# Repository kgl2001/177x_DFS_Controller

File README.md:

# Acorn BBC Micro 177x Disc Interface module
This module can be used in place of a 8271 disc controller in the BBC micro computer.

Some general notes:

* The source files are to be used with KiCAD v9.0.0 or later.
* The Rev03 PCB is only marginally bigger than the original 8271 IC that it replaces. This should prevent the board from clashing with other upgrades, like Speech or ROM / RAM expansion boards.
* The gerber files have been optimised for fabrication by JLCPCB. In particular, there is a 8mmx8mm silkscreen box on the top front of the PCB. This is to allow a 2D barcode, with unique serial number to be printed on the PCB.
* If you want the barcode to be added, then make sure to select this option in the 'Mark on PCB' field, and make sure to select 'Specify position' in the '2D Barcode Position' field, otherwise you will end up with a white 8mm x 8mm box printed on your PCB and a 8mm x 8mm barcode printed at a position of JLCPCBs choosing. Thrust me on this!
* If you don't want the barcode added, then remove the 8mm x 8mm box from the silkscreen layer and regenerate the gerbers. Otherwise you will end up with a white 8mm x 8mm box printed on your PCB.
* A combined CPL / BOM file is included in the gerber directory. Again, this is for use with JLCPCB, if you want to use their PCBA (PCB Assembly) to solder on all the SMD parts.
* You will need to source a suitable 1770 / 1772 disc controller IC to install on the board. These are becoming increasingly difficult to find at a reasonable price.
* Additional modifications (including the installation of additional ICs) may be required to the beeb motherboard. These modifications are detailed in the attached Acorn_1770DiscIFUpgradeKit.pdf document 

Please refer to the following discussion on Stardot for further details: [https://stardot.org.uk/forums/viewtopic.php?f=3&t=18815](https://stardot.org.uk/forums/viewtopic.php?t=30150)

## Author

The Disc Interface module is developed and maintained by Ken Lowe.
    
## Hardware License (Creative Commons BY-SA 4.0)

Please see the following link for details: https://creativecommons.org/licenses/by-sa/4.0/

You are free to:

Share - copy and redistribute the material in any medium or format
Adapt - remix, transform, and build upon the material
for any purpose, even commercially.

This license is acceptable for Free Cultural Works.

The licensor cannot revoke these freedoms as long as you follow the license terms.

Under the following terms:

Attribution - You must give appropriate credit, provide a link to the license, and indicate if changes were made. You may do so in any reasonable manner, but not in any way that suggests the licensor endorses you or your use.

ShareAlike - If you remix, transform, or build upon the material, you must distribute your contributions under the same license as the original.

No additional restrictions - You may not apply legal terms or technological measures that legally restrict others from doing anything the license permits.

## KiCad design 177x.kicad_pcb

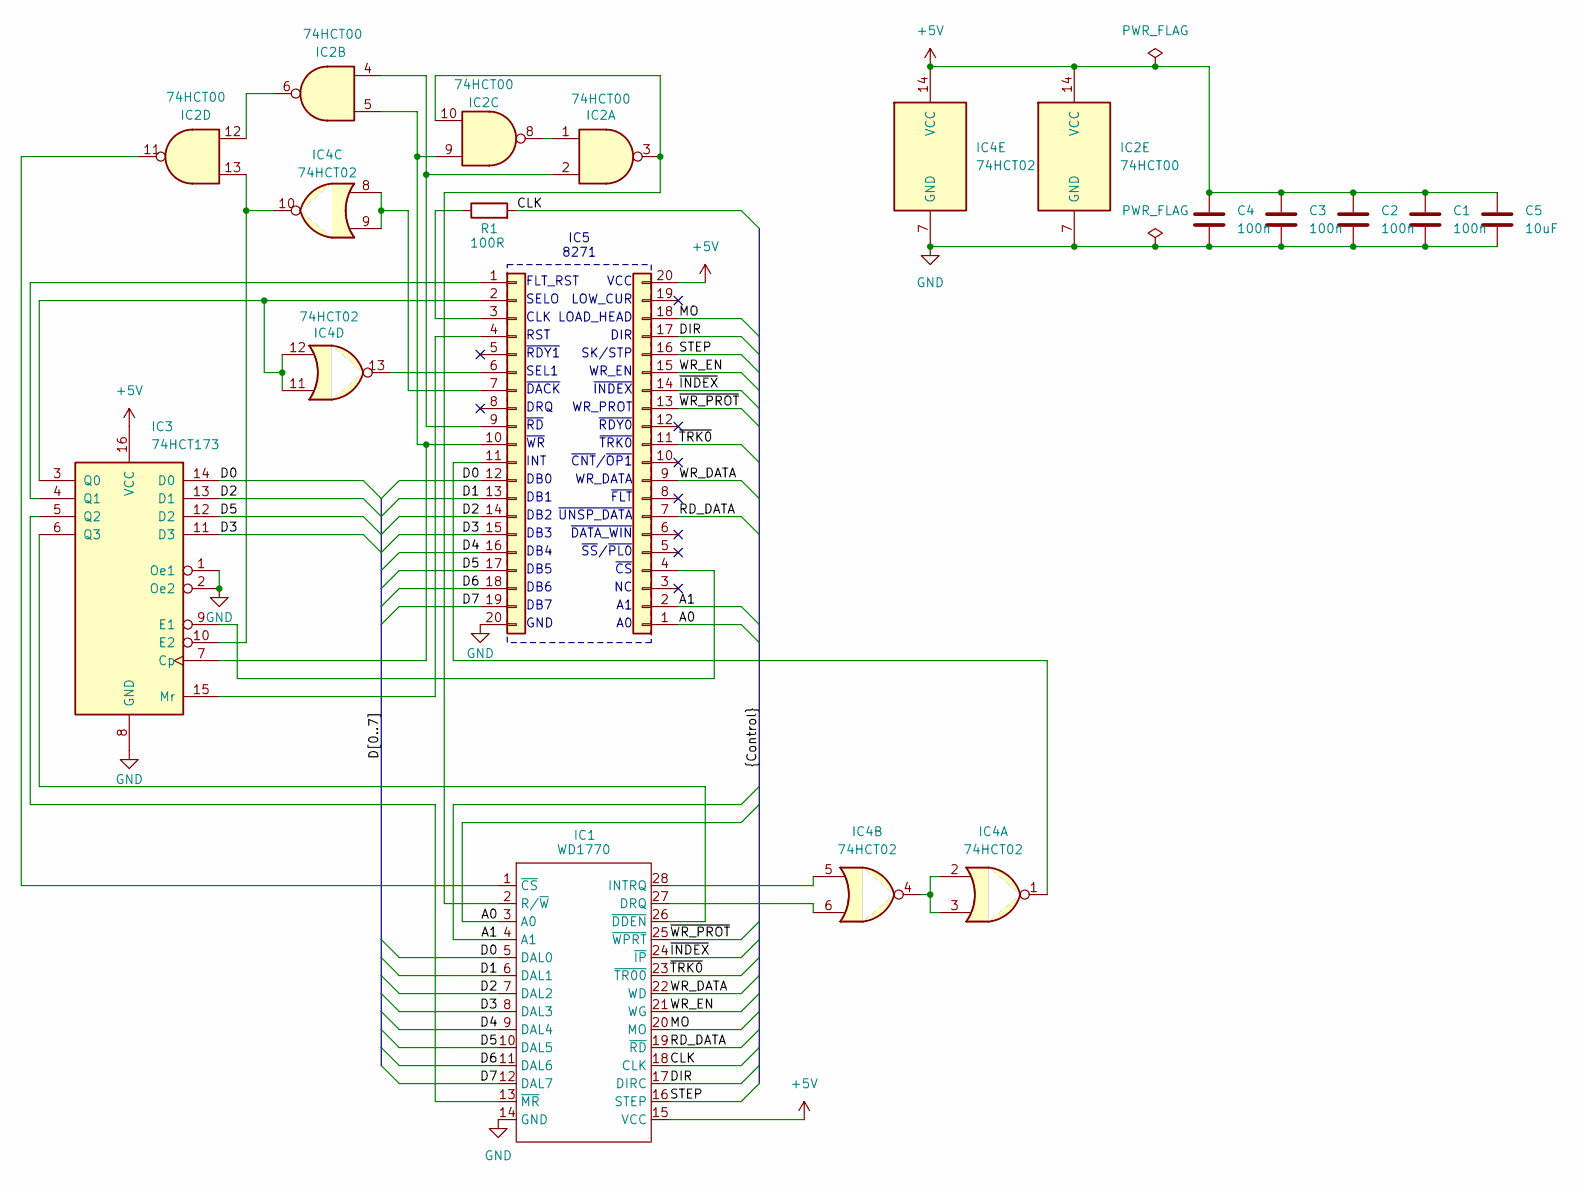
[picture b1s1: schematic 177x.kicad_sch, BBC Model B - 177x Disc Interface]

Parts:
C1, C2, C3, C4: 100n; C_0603_1608Metric; JLC Part Number C14663
C5: 10uF; C_0805_2012Metric; JLC Part Number C15850
IC1: WD1770; DIP-28_W15.24mm_Socket
IC2: 74HCT00; SOIC-14_3.9x8.7mm_P1.27mm; JLC Part Number C6764
IC3: 74HCT173; SOIC-16_3.9x9.9mm_P1.27mm; JLC Part Number C3827006
IC4: 74HCT02; SOIC-14_3.9x8.7mm_P1.27mm; JLC Part Number C471050
J1: Conn_01x20; PinHeader_1_20_P2.54mm_Vertical
J2: Conn_01x20; PinHeader_21_40_P2.54mm_Vertical
R1: 100R; R_0603_1608Metric; JLC Part Number C22775

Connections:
+5V: C1.1, C2.1, C3.1, C4.1, C5.1, IC1.15 (VCC), IC2.14 (VCC), IC3.16 (VCC), IC4.14 (VCC), J2.20
/A0: IC1.3 (A0), J2.1
/A1: IC1.4 (A1), J2.2
/CLK: IC1.18 (CLK), R1.2
/D0: IC1.5 (DAL0), IC3.14 (D0), J1.12
/D1: IC1.6 (DAL1), J1.13
/D2: IC1.7 (DAL2), IC3.13 (D1), J1.14
/D3: IC1.8 (DAL3), IC3.11 (D3), J1.15
/D4: IC1.9 (DAL4), J1.16
/D5: IC1.10 (DAL5), IC3.12 (D2), J1.17
/D6: IC1.11 (DAL6), J1.18
/D7: IC1.12 (DAL7), J1.19
/DIR: IC1.17 (DIRC), J2.17
/MO: IC1.20 (MO), J2.18
/RD_DATA: IC1.19 (~RD), J2.7
/STEP: IC1.16 (STEP), J2.16
/WR_DATA: IC1.22 (WD), J2.9
/WR_EN: IC1.21 (WG), J2.15
/~INDEX: IC1.24 (~IP), J2.14
/~TRK0: IC1.23 (~TR00), J2.11
/~WR_PROT: IC1.25 (~WPRT), J2.13
GND: C1.2, C2.2, C3.2, C4.2, C5.2, IC1.14 (GND), IC2.7 (GND), IC3.1 (Oe1), IC3.2 (Oe2), IC3.8 (GND), IC4.7 (GND), J1.20
unnamed: IC1.27 (DRQ), IC4.6
unnamed: IC1.28 (INTRQ), IC4.5
unnamed: IC1.2 (R/~W), IC2.3, IC2.10
unnamed: IC1.1 (~CS), IC2.11
unnamed: IC1.26 (~DDEN), IC3.6 (Q3)
unnamed: IC1.13 (~MR), IC3.5 (Q2)
unnamed: IC2.1, IC2.8
unnamed: IC2.6, IC2.12
unnamed: IC2.5, IC2.9, IC3.7 (Cp), J1.10
unnamed: IC3.9 (E1), J2.4
unnamed: IC2.13, IC3.10 (E2), IC4.10
unnamed: IC3.15 (Mr), J1.4
unnamed: IC3.3 (Q0), IC4.11, IC4.12, J1.2
unnamed: IC3.4 (Q1), J1.1
unnamed: IC4.2, IC4.3, IC4.4
unnamed: J1.3, R1.1
unnamed: IC4.13, J1.6
unnamed: IC4.8, IC4.9, J1.7
unnamed: IC2.2, IC2.4, J1.9
unnamed: IC4.1, J1.11

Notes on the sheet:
~{CS}
~{DACK}
DIR
~{RDY1}
GND
SK/STP
RST
WR_EN
INT
DB7
LOAD_HEAD
~{FLT}
WR_PROT
~{TRK0}
~{INDEX}
DB4
LOW_CUR
DRQ
SELO
WR_DATA
DB6
~{DATA_WIN}
DB1
DB2
~{SS}/~{PL0}
DB0
~{CNT}/~{OP1}
~{RDY0}
CLK
~{WR}
FLT_RST
DB3
~{UNSP_DATA}
~{RD}
VCC
SEL1
IC5 8271
DB5

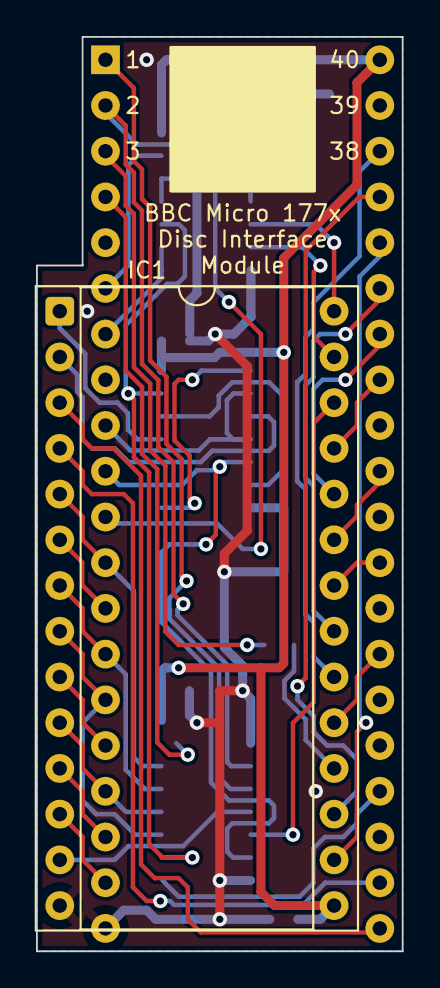
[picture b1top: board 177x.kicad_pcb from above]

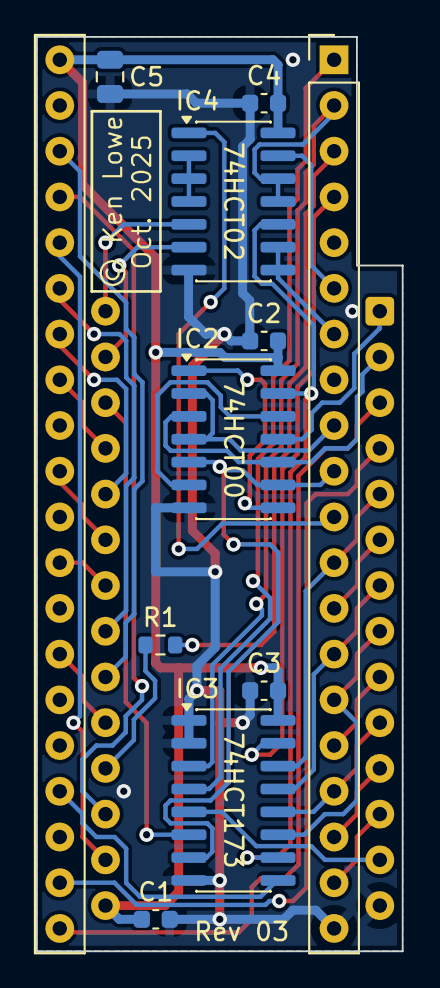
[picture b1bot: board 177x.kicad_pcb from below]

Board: 2 copper layers, 20.3 x 50.8 mm, 12 parts (11 on the bottom side), 42 nets.

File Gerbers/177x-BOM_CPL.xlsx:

Designator | LCSC Part # | Footprint | JLCValue | Mid X | Mid Y | Rotation | Layer | Val | Package
C1 | C14663 | 0603 | 100n | 110.236 | -84.835999999999999 | 180 | bottom | 100n | C_0603_1608Metric
C2 | C14663 | 0603 | 100n | 104.218 | -52.704999999999998 | 0 | bottom | 100n | C_0603_1608Metric
C3 | C14663 | 0603 | 100n | 104.218 | -72.135999999999996 | 0 | bottom | 100n | C_0603_1608Metric
C4 | C14663 | 0603 | 100n | 104.218 | -39.497 | 0 | bottom | 100n | C_0603_1608Metric
C5 | C15850 | 0805 | 10uF | 112.776 | -38.033999999999999 | -90 | bottom | 10uF | C_0805_2012Metric
IC2 | C6764 | SOIC-14 | 74HCT00 | 105.91800000000001 | -58.165999999999997 | -90 | bottom | 74HCT00 | SOIC-14_3.9x8.7mm_P1.27mm
IC3 | C3827006 | SOIC-16 | 74HCT173 | 105.91800000000001 | -78.231999999999999 | -90 | bottom | 74HCT173 | SOIC-16_3.9x9.9mm_P1.27mm
IC4 | C471050 | SOIC-14 | 74HCT02 | 105.91800000000001 | -44.957999999999998 | -90 | bottom | 74HCT02 | SOIC-14_3.9x8.7mm_P1.27mm
R1 | C22775 | 0603 | 100R | 109.982 | -69.596000000000004 | 0 | bottom | 100R | R_0603_1608Metric

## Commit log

2025-03-10 Add License
2025-03-10 Added .pdf copy of schematic
2025-03-10 Correct typo in README.md
2025-10-27 Revised PCB layout
    PCB dimensions reduced. Overhang now significantly reduced.

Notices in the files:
177x.kicad_pcb:
© Ken Lowe
